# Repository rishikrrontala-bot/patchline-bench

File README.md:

[Live app](https://patchline-bench.vercel.app/) · [Source repository](https://github.com/rishikrrontala-bot/patchline-bench)

# Patchline Bench

Built by Rishik Rontala. A nonclinical sensing and signal-review prototype, kept separate from prior Patchline hackathon editions.

Run `npm start`, then open http://127.0.0.1:8790. Generate a reproducible steady, coordinated-shift or sensor-fault window. Inspect four charts and local model likelihoods; review an eligible synthetic window and log a virtual rehearsal. Import JSON locally or explicitly choose a USB serial port in a compatible browser. Bench and imported windows are always held. No hardware actuation or therapeutic dose exists.

The local classifier was trained from scratch on 1,200 simulated runs, selected using 300 validation runs, and evaluated on 300 independent test runs. Accuracy 89.7%, macro F1 89.4%. It missed 31 of 100 injected sensor faults; these metrics do not establish infection detection, medical benefit, or generalization to real sensors. A separate quality gate flags missing/held signals and prevents rehearsal for estimated faults or low confidence. Its review threshold is an explicit demo policy, not a clinical threshold.

`npm test` runs 35 independent software tests. `python3 tools/board.py` produces the passive PCB draft, netlist and drawing with layer-aware connectivity checks. `node tools/generate-data.mjs` and `python3 tools/train.py` reproduce the simulation/model. Both firmware modes pass native host-stub checks, including I²C failures. Both firmware modes compile for the selected ESP32; hardware measurements remain pending.

Read [LIMITATIONS.md](LIMITATIONS.md), [hardware/WIRING.md](hardware/WIRING.md) and [firmware/README.md](firmware/README.md) before touching hardware. The board has no input protection or patient-contact design and still requires KiCad DRC and electrical review.

Featherless GLM 5.2 supplied an initial simulator implementation; it was corrected and tested locally. Featherless DeepSeek-V3.2 supplied an independent firmware review; verified findings and rejected errors are recorded under proof/. Secrets stay outside this project. The shared cumulative Featherless cap is $10; current conservative ledger estimate approximately $0.5811. Adaption is limited to 100 existing credits, with no purchases. Its proposed job fine-tunes a bench evidence summarizer; the numerical model above is already trained locally. Cloud training status is tracked separately and must not be represented as complete before confirmation.

The exploded assembly uses original vector illustrations, with real hub routing underneath. Click **Assemble patch** to close the six open concept layers, then **Open layers** to reverse it. The same button supports keyboard activation; reduced motion switches views immediately. Scrolling does not control the animation. A standalone version is packaged at `artifacts/Patchline-Bench.html`; direct browser testing of that file was blocked by the browser file-URL policy, while the source app was verified through its normal local preview.

## Devpost draft

The local story is in [devpost-submission.md](devpost-submission.md). It separates working software from proposed business features, unassembled hardware, and the pending Adaption training experiment. Final event entry and the public five-minute voiceover video remain separate steps.

## Demo videos and voiceover scripts

- [2:30 silent pitch demo](artifacts/demo/Patchline-Bench-2m30s-silent.mp4) · [matching script](docs/VOICEOVER-SHORT.md)
- [5:00 silent full walkthrough](artifacts/demo/Patchline-Bench-5m00s-silent.mp4) · [matching script](docs/VOICEOVER-FULL.md)

Both videos combine actual browser captures with source/evidence cards. They are edited walkthroughs, not physical hardware footage. They contain no audio so Rishik can record his own narration. Exact duration, silent streams and full decoding were verified in `proof/demo-verification.json`. Record each timed chapter, place the voiceover over the corresponding MP4, and export before uploading a public/unlisted submission video. The five-minute version covers the Next Founders rubric; the shorter cut is for pitches and other submission limits.

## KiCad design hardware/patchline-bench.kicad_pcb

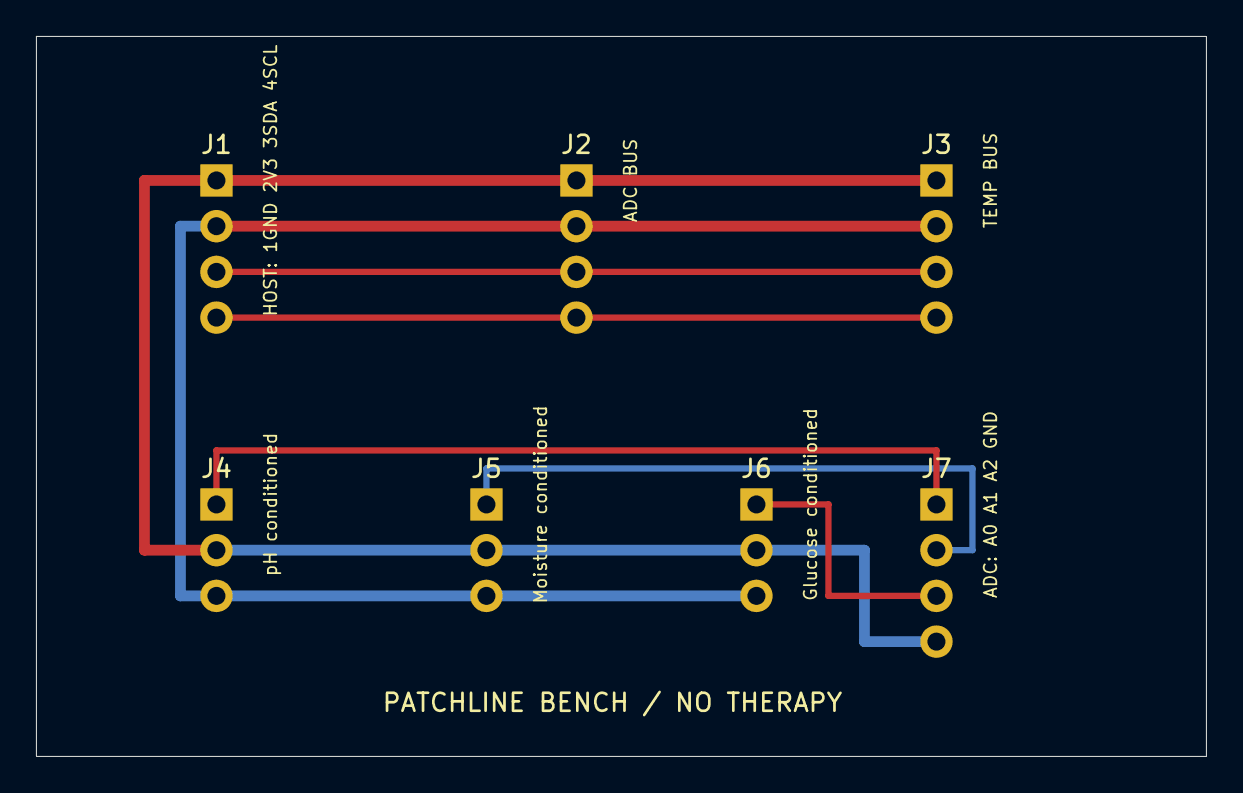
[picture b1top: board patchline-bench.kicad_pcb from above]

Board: 2 copper layers, 65.0 x 40.0 mm, 7 parts (0 on the bottom side), 7 nets.

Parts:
J1: HOST: 1GND 2V3 3SDA 4SCL; PinHeader_1x04_P2.54mm_Vertical
J2: ADC BUS; PinHeader_1x04_P2.54mm_Vertical
J3: TEMP BUS; PinHeader_1x04_P2.54mm_Vertical
J4: pH conditioned; PinHeader_1x03_P2.54mm_Vertical
J5: Moisture conditioned; PinHeader_1x03_P2.54mm_Vertical
J6: Glucose conditioned; PinHeader_1x03_P2.54mm_Vertical
J7: ADC: A0 A1 A2 GND; PinHeader_1x04_P2.54mm_Vertical

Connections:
+3V3: J1.2, J2.2, J3.2, J4.3, J5.3, J6.3
GLUCOSE_SIG: J6.1, J7.3
GND: J1.1, J2.1, J3.1, J4.2, J5.2, J6.2, J7.4
MOIST_SIG: J5.1, J7.2
PH_SIG: J4.1, J7.1
SCL: J1.4, J2.4, J3.4
SDA: J1.3, J2.3, J3.3
